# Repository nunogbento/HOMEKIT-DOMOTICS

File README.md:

# HOMEKIT-DOMOTICS

Personal collection of home-automation hardware and firmware around Apple HomeKit,
spanning multiple generations of boards and HomeKit integration techniques.

## Project layout

Each top-level folder is one project. Projects with a custom PCB have:

```
<Project>/
├── firmware/      one subfolder per firmware version (generation)
├── circuit/       PCB design files (.brd / .sch / .cam)
└── enclosure/     3D-printable bodies (where applicable)
```

Projects without a custom PCB omit `circuit/`, and use `enclosure/` only if a
3D-printed body exists.

## Active projects

### [PCCWDplus](PCCWDplus/) — custom PCB
Main panel board. Succession: MQTT (ESP8266) → HomeSpan (ESP32-C5).
Gen 2 (HAP/ESP8266) was attempted but failed; see archive notes.
- `firmware/Mqtt.MordomusESP8266/` — gen 1, MQTT/ESP8266 — **deployed**
- `firmware/HSPCCWDplus/` — gen 3, HomeSpan/ESP32-C5 — **WIP**, pin-compatible drop-in

### [MultiAccessory](MultiAccessory/) — custom PCB
Multi-device controller board. Gen 2 still deployed, gen 3 in progress.
- `firmware/HKMultiAccessory/` — gen 2, HAP/ESP8266 — **deployed**
- `firmware/HSPMultiAccessory/` — gen 3, HomeSpan/ESP32-C5 — **WIP**
- `firmware/HKSprinklerValve/` — gen 2 valve variant on the same board

### [ESP8266-ADC](ESP8266-ADC/) — custom PCB
Shared ESP8266-with-ADC board used for analog sensing applications.
- `firmware/HKSolarPanel/` — gen 2, HAP/ESP8266 — **deployed**, no successor planned
- `firmware/mqtt-SolarPanel/` — gen 1, archived firmware
- `firmware/Mqtt.ESP8266PlantComputer/` — gen 1, archived firmware

### [HSPCCWD](HSPCCWD/) — no custom hardware
HomeSpan reference implementation on a bare ESP32 devkit, serial-only.

### [ESP32Door](ESP32Door/) — no custom hardware
Door sensor using an off-the-shelf ESP32 module + 3D-printed enclosure.

### [Feeder](Feeder/) — no custom hardware, 3D-printed body
- `firmware/HKFEEDER/` — current
- `firmware/mqtt-RabitFeeder/` — earlier version

## HomeKit firmware generations

| Gen | Stack           | Chip         | Status                                |
|-----|-----------------|--------------|---------------------------------------|
| 1   | MQTT bridge     | ESP8266      | Mqtt.MordomusESP8266 still deployed   |
| 2   | Arduino-HomeKit | ESP8266      | HKMultiAccessory, HKSolarPanel still deployed; HKPCCWD archived (failed) |
| 3   | HomeSpan        | ESP32 / C5   | HSPCCWDplus, HSPMultiAccessory — WIP  |

Gen 2 failed on the PCCWD board because the ESP8266 could not handle HomeKit
at that board's accessory complexity. That's why the PCCWD lineage jumps
directly from gen 1 (MQTT) to gen 3 (HomeSpan).

## archive/

Everything superseded, retired, unfinished, unrelated, or not tied to an
active hardware project. Includes:
- `HKPCCWD/` (gen 2 failure)
- Early MQTT experiments (lightbulbs, rollerblinds, power meter, etc.)
- Side experiments (CameraWebServer, ESP-32CAM, SONOFFAPI, WaterDetector)
- `Tradfri-ICC-1/` — reverse-engineering research that informed MultiAccessory
- `MordomusAPI/`, `PowerMeter/`, `pccwdapi/`, `node-red-contrib-pccwd/` — no longer used
- `homebridge-host/` — Homebridge configuration, Node-RED flows, backups

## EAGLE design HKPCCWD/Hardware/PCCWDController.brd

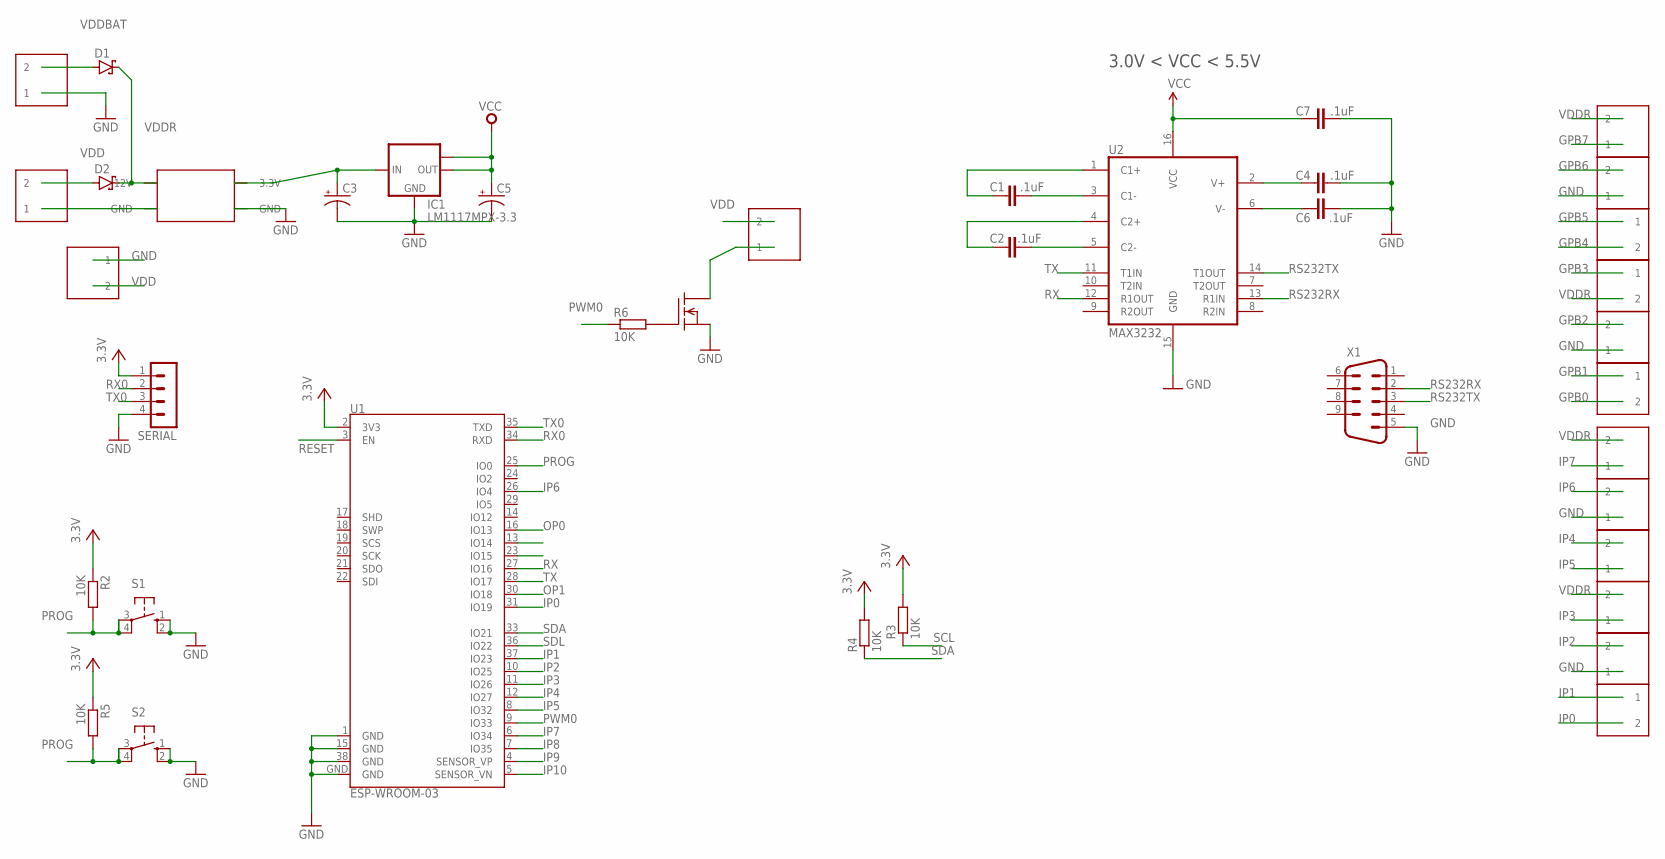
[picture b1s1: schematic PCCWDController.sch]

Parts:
C1, C2, C4, C6, C7: .1uF; 0603-CAP
C3, C5: 100UF-25V-20%(PTH); CPOL-RADIAL-100UF-25V
D1, D2: SCHOTTKY-DIODESMC; SMC
G: FDS5680; SO-8
IC1: LM1117MPX-3.3; SOT223
PWR1: MP2307-MINI-360
PWR_IN, PWR_IN1, PWR_IN2, PWR_IN3, PWR_IN4, PWR_IN5, PWR_IN6, PWR_IN7, PWR_IN8, PWR_IN9, PWR_IN10, PWR_IN11, PWR_IN12, PWR_IN13, PWR_IN14: KF350-P2; KF350-2P
PWR_INBAT: KF350-P2; KF350-2P
R2, R3, R4, R5, R6: 10K; R0603
S1, S2: 10-XX; B3F-10XX
SERIAL: MA04-1
U1: ESP-WROOM-03
U2: MAX3232; SO016
X1: M09HP

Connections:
+3V3: C5.1 (+), C7.1, IC1.2 (OUT), IC1.TAB (OUT1), R2.1, R3.2, R4.2, R5.1, SERIAL.1, U2.16 (VCC)
C1+: C1.1, U2.1 (C1+)
C1-: C1.2, U2.3 (C1-)
C2+: C2.1, U2.4 (C2+)
C2-: C2.2, U2.5 (C2-)
DG: G.5 (D), G.6 (D), G.7 (D), G.8 (D), PWR_IN1.1
GND: C3.2 (-), C4.2, C5.2 (-), C6.2, C7.2, G.1 (S), G.2 (S), G.3 (S), IC1.1 (GND), PWR1.GND@1 (GND), PWR1.GND@2 (GND), PWR_IN.1, PWR_IN2.1, PWR_IN5.1, PWR_IN8.1, PWR_IN12.1, PWR_IN14.1, PWR_INBAT.1, S1.1 (S), S1.2 (S1), S2.1 (S), S2.2 (S1), SERIAL.4, U1.1 (GND), U1.15 (GND), U1.38 (GND), U1.GND, U2.15 (GND), X1.5
GPB0: PWR_IN6.2
GPB1: PWR_IN6.1
GPB2: PWR_IN5.2
GPB3: PWR_IN7.1
GPB4: PWR_IN9.2
GPB5: PWR_IN9.1
GPB6: PWR_IN8.2
GPB7: PWR_IN4.1
IP0: PWR_IN11.2, U1.31 (IO19)
IP1: PWR_IN11.1, U1.37 (IO23)
IP2: PWR_IN12.2, U1.10 (IO25)
IP3: PWR_IN13.1, U1.11 (IO26)
IP4: PWR_IN3.2, U1.12 (IO27)
IP5: PWR_IN3.1, U1.8 (IO32)
IP6: PWR_IN2.2, U1.26 (IO4)
IP7: PWR_IN10.1, U1.6 (IO34)
IP8: U1.7 (IO35)
IP9: U1.4 (SENSOR_VP)
IP10: U1.5 (SENSOR_VN)
unnamed: G.4 (G), R6.2
OP0: U1.16 (IO13)
OP1: U1.30 (IO18)
PROG: R2.2, R5.2, S1.3, S1.4 (P1), S2.3, S2.4 (P1), U1.25 (IO0)
PWM0: R6.1, U1.9 (IO33)
RESET: U1.3 (EN)
RS232RX: U2.13 (R1IN), X1.2
RS232TX: U2.14 (T1OUT), X1.3
RVCC: C3.1 (+), IC1.3 (IN), PWR1.3.3V
RX: U1.27 (IO16), U2.12 (R1OUT)
RX0: SERIAL.2, U1.34 (RXD)
SCL: R3.1
SDA: R4.1, U1.33 (IO21)
SDL: U1.36 (IO22)
TX: U1.28 (IO17), U2.11 (T1IN)
TX0: SERIAL.3, U1.35 (TXD)
V+: C4.1, U2.2 (V+)
V-: C6.1, U2.6 (V-)
VCC: U1.2 (3V3)
VDD: D2.A, PWR_IN.2, PWR_IN1.2, PWR_IN14.2
VDDBAT: D1.A, PWR_INBAT.2
VDDR: D1.C, D2.C, PWR1.12V, PWR_IN4.2, PWR_IN7.2, PWR_IN10.2, PWR_IN13.2

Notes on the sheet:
3.0V < VCC < 5.5V

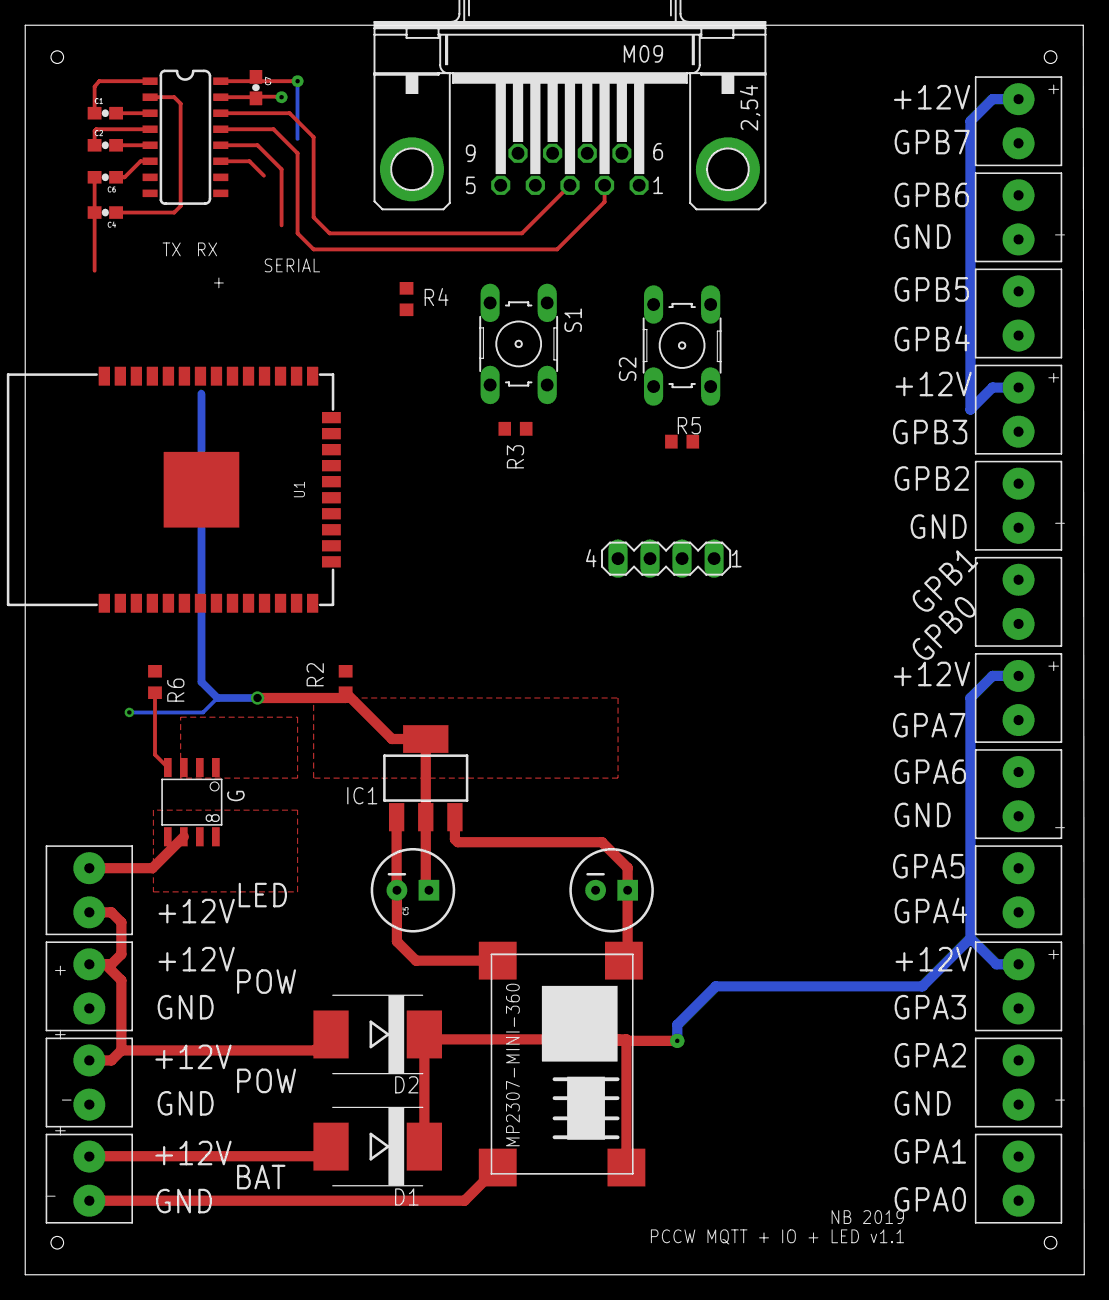
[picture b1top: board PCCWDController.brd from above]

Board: 2 copper layers, 83.9 x 99.0 mm, 39 parts (0 on the bottom side), 31 nets.

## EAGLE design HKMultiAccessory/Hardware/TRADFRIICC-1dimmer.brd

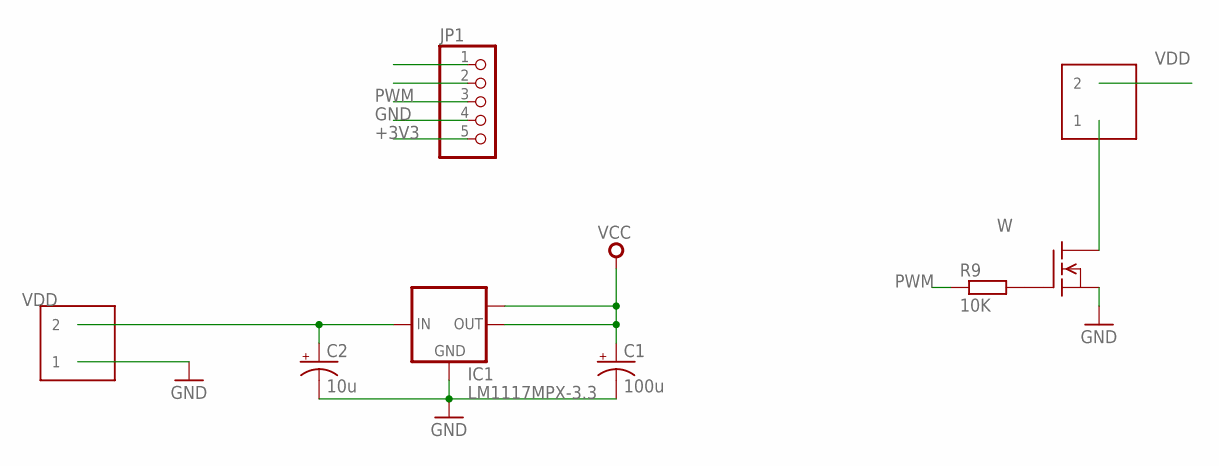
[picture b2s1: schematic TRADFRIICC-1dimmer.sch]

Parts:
C1: 100u; CT3528
C2: 10u; C/6032-28R
IC1: LM1117MPX-3.3; SOT223
JP1: PINHD-1X55X2MM; 1_05X2MM
PWR_IN, PWR_IN1: KF350-P2; KF350-2P
R9: 10K; R0603
W: FDS5680; SO-8

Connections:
+3V3: C1.+, IC1.2 (OUT), IC1.TAB (OUT1), JP1.5
DW: PWR_IN1.1, W.5 (D), W.6 (D), W.7 (D), W.8 (D)
GND: C1.-, C2.-, IC1.1 (GND), JP1.4, PWR_IN.1, W.1 (S), W.2 (S), W.3 (S)
unnamed: R9.2, W.4 (G)
PWM: JP1.3, R9.1
VDD: C2.+, IC1.3 (IN), PWR_IN.2, PWR_IN1.2

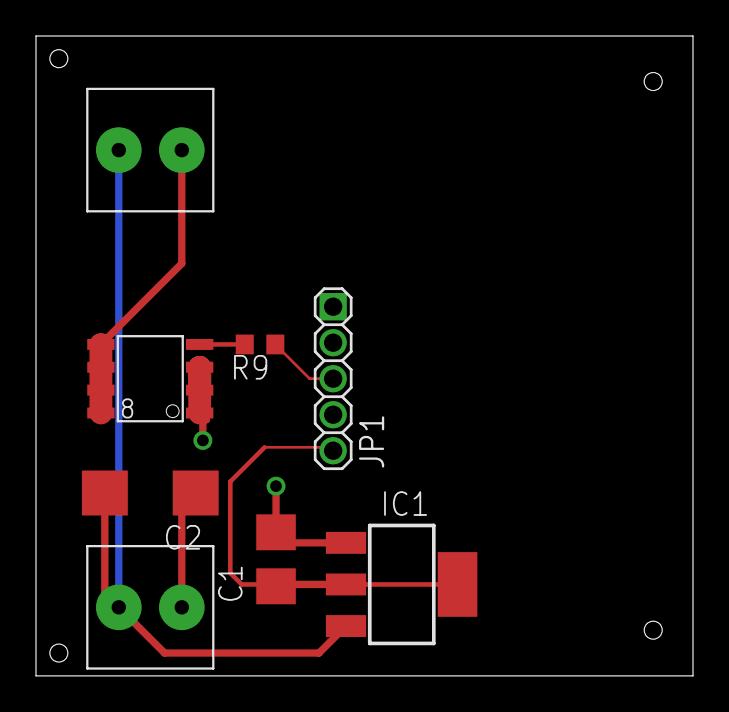
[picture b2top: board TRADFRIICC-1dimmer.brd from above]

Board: 2 copper layers, 36.5 x 35.5 mm, 8 parts (0 on the bottom side), 6 nets.

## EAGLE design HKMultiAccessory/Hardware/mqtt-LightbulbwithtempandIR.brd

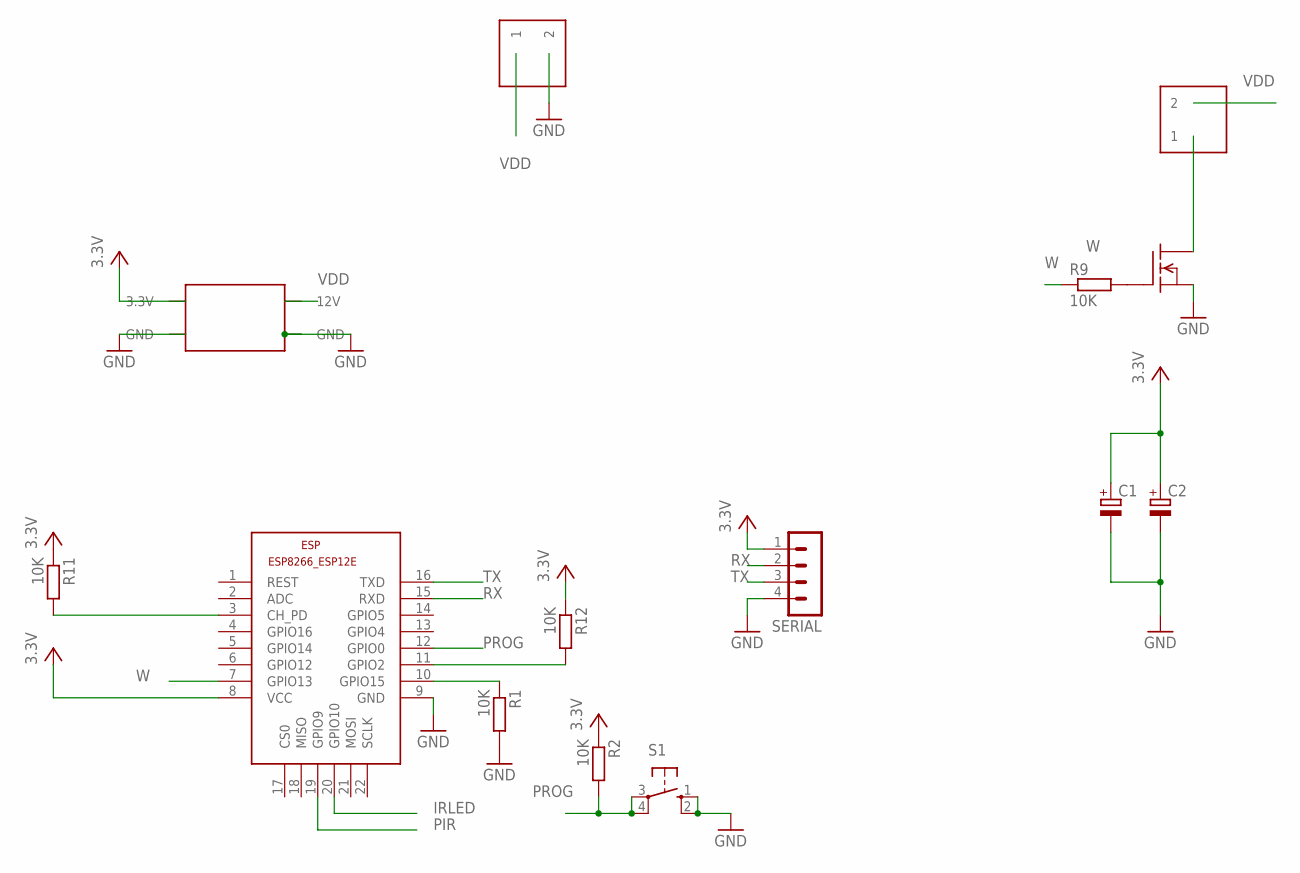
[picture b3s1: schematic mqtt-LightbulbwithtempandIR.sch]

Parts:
C1, C2: CPOL-EUE2-5; E2-5
ESP: ESP8266-12EESP8266-ESP12E; ESP8266-ESP12E
PWR1: MP2307-MINI-360
PWR_IN1, PWR_IN2: KF350-P2; KF350-2P
R1, R2, R9, R11, R12: 10K; R0603
S1: 10-XX; B3F-10XX
SERIAL: MA04-1
W: FDS5680; SO-8

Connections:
DW: PWR_IN1.1, W.5 (D), W.6 (D), W.7 (D), W.8 (D)
GND: C1.-, C2.-, ESP.9 (GND), PWR1.GND@1 (GND), PWR1.GND@2 (GND), PWR_IN2.2, R1.2, S1.1 (S), S1.2 (S1), SERIAL.4, W.1 (S), W.2 (S), W.3 (S)
IRLED: ESP.20 (GPIO10)
unnamed: ESP.10 (GPIO15), R1.1
unnamed: ESP.3 (CH_PD), R11.2
unnamed: ESP.11 (GPIO2), R12.2
unnamed: R9.2, W.4 (G)
PIR: ESP.19 (GPIO9)
PROG: ESP.12 (GPIO0), R2.2, S1.3, S1.4 (P1)
RX: ESP.15 (RXD), SERIAL.2
TX: ESP.16 (TXD), SERIAL.3
VCC: C1.+, C2.+, ESP.8 (VCC), PWR1.3.3V, R2.1, R11.1, R12.1, SERIAL.1
VDD: PWR1.12V, PWR_IN1.2, PWR_IN2.1
W: ESP.7 (GPIO13), R9.1

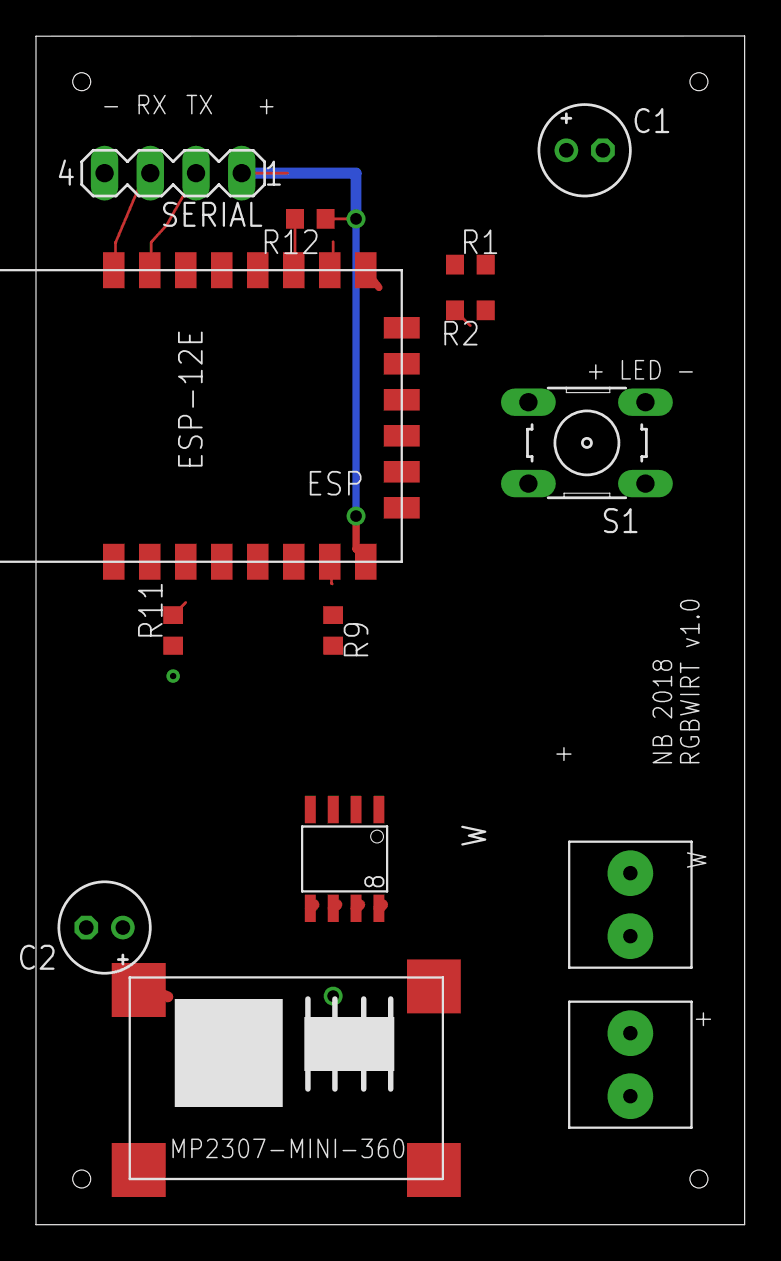
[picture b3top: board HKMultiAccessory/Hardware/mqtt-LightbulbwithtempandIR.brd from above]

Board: 2 copper layers, 39.4 x 66.0 mm, 14 parts (0 on the bottom side), 12 nets.

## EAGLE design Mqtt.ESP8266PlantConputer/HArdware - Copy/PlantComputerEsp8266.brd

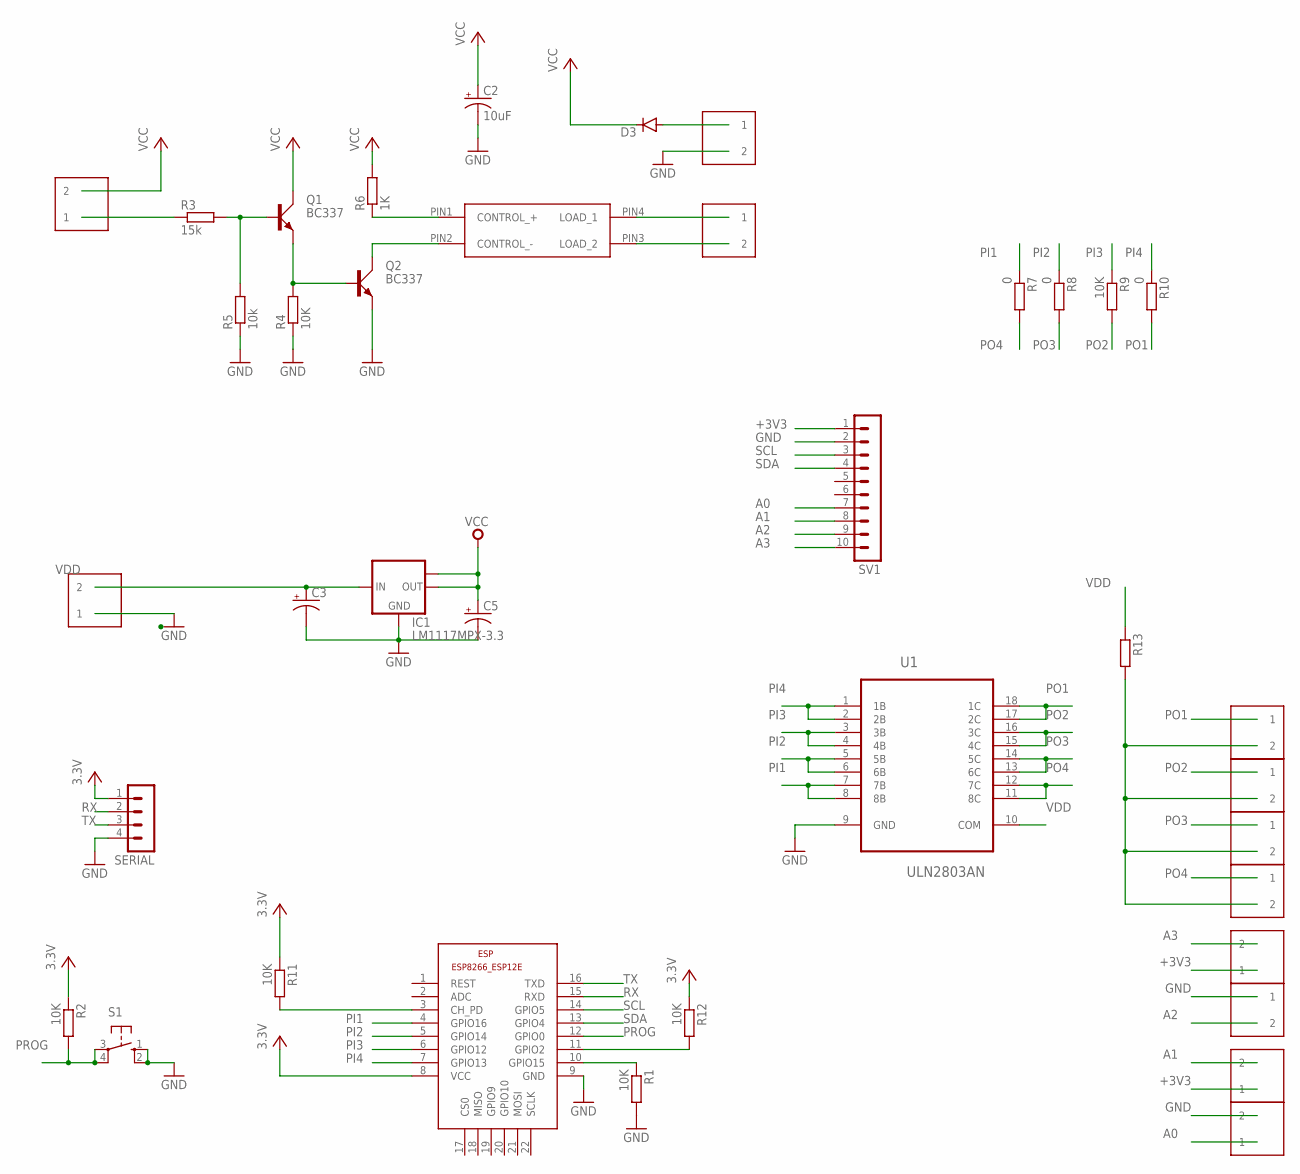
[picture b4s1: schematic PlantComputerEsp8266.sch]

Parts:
C2: 10uF; CPOL-RADIAL-2.5MM-5MM
C3, C5: 100UF-25V-20%(PTH); CPOL-RADIAL-100UF-25V
D3: DIODE-DO214AC; DO214AC
ESP: ESP8266-12EESP8266-ESP12E; ESP8266-ESP12E
IC1: LM1117MPX-3.3; SOT223
PWR_IN, PWR_IN2, PWR_IN4, PWR_IN5, PWR_IN6, PWR_IN7, PWR_IN8, PWR_IN9, PWR_IN10: KF350-P2; KF350-2P
Q1, Q2: BC337; SOT54A
R1, R2, R9, R11, R12: 10K; R0603
R3: 15k; R0805
R4: 10K; R0805
R5: 10k; R0805
R6: 1K; R0805
R7, R8, R10: 0; R0603
R13: R-EU_R0603; R0603
S1: 10-XX; B3F-10XX
SERIAL: MA04-1
SV1: MA10-1
U1: ULN2803AN; DIP254P762X393-18
U$1: OPTO-RELAY-CPC1017N; SOP-4
U$2, U$3, U$4: KF350-P2; KF350-2P

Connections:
+3V3: C5.1 (+), ESP.8 (VCC), IC1.2 (OUT), IC1.TAB (OUT1), PWR_IN5.1, PWR_IN10.1, R2.1, R11.1, R12.1, SERIAL.1, SV1.1
A0: PWR_IN2.1, SV1.7
A1: PWR_IN10.2, SV1.8
A2: PWR_IN6.2, SV1.9
A3: PWR_IN5.2, SV1.10
GND: C2.2 (-), C3.2 (-), C5.2 (-), ESP.9 (GND), IC1.1 (GND), PWR_IN.1, PWR_IN2.2, PWR_IN6.1, Q2.E, R1.2, R4.1, R5.1, S1.1 (S), S1.2 (S1), SERIAL.4, SV1.2, U1.9 (GND), U$3.2
unnamed: Q1.B, R3.2, R5.2
unnamed: ESP.10 (GPIO15), R1.1
unnamed: ESP.3 (CH_PD), R11.2
unnamed: ESP.11 (GPIO2), R12.2
unnamed: Q1.E, Q2.B, R4.2
unnamed: Q2.C, U$1.PIN2 (CONTROL_-)
unnamed: R6.1, U$1.PIN1 (CONTROL_+)
unnamed: R3.1, U$4.1
unnamed: U$1.PIN4 (LOAD_1), U$2.1
unnamed: D3.A, U$3.1
unnamed: U$1.PIN3 (LOAD_2), U$2.2
unnamed: PWR_IN4.2, PWR_IN7.2, PWR_IN8.2, PWR_IN9.2, R13.2
PI1: ESP.4 (GPIO16), R7.1, U1.7 (7B), U1.8 (8B)
PI2: ESP.5 (GPIO14), R8.1, U1.5 (5B), U1.6 (6B)
PI3: ESP.6 (GPIO12), R9.1, U1.3 (3B), U1.4 (4B)
PI4: ESP.7 (GPIO13), R10.1, U1.1 (1B), U1.2 (2B)
PO1: PWR_IN4.1, R10.2, U1.17 (2C), U1.18 (1C)
PO2: PWR_IN8.1, R9.2, U1.15 (4C), U1.16 (3C)
PO3: PWR_IN9.1, R8.2, U1.13 (6C), U1.14 (5C)
PO4: PWR_IN7.1, R7.2, U1.11 (8C), U1.12 (7C)
PROG: ESP.12 (GPIO0), R2.2, S1.3, S1.4 (P1)
RX: ESP.15 (RXD), SERIAL.2
SCL: ESP.14 (GPIO5), SV1.3
SDA: ESP.13 (GPIO4), SV1.4
TX: ESP.16 (TXD), SERIAL.3
VCC: C2.1 (+), D3.C, Q1.C, R6.2, U$4.2
VDD: C3.1 (+), IC1.3 (IN), PWR_IN.2, R13.1, U1.10 (COM)

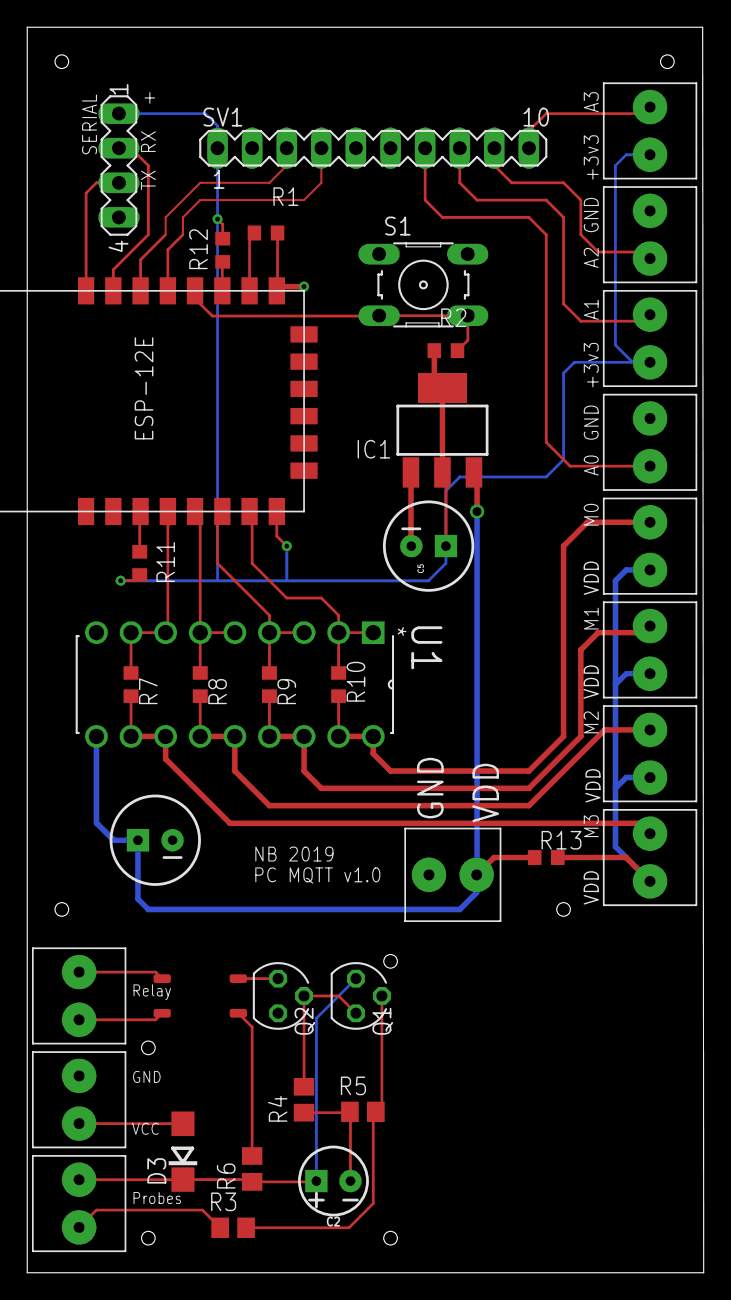
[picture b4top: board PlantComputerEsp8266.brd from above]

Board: 2 copper layers, 49.7 x 91.4 mm, 38 parts (0 on the bottom side), 33 nets.

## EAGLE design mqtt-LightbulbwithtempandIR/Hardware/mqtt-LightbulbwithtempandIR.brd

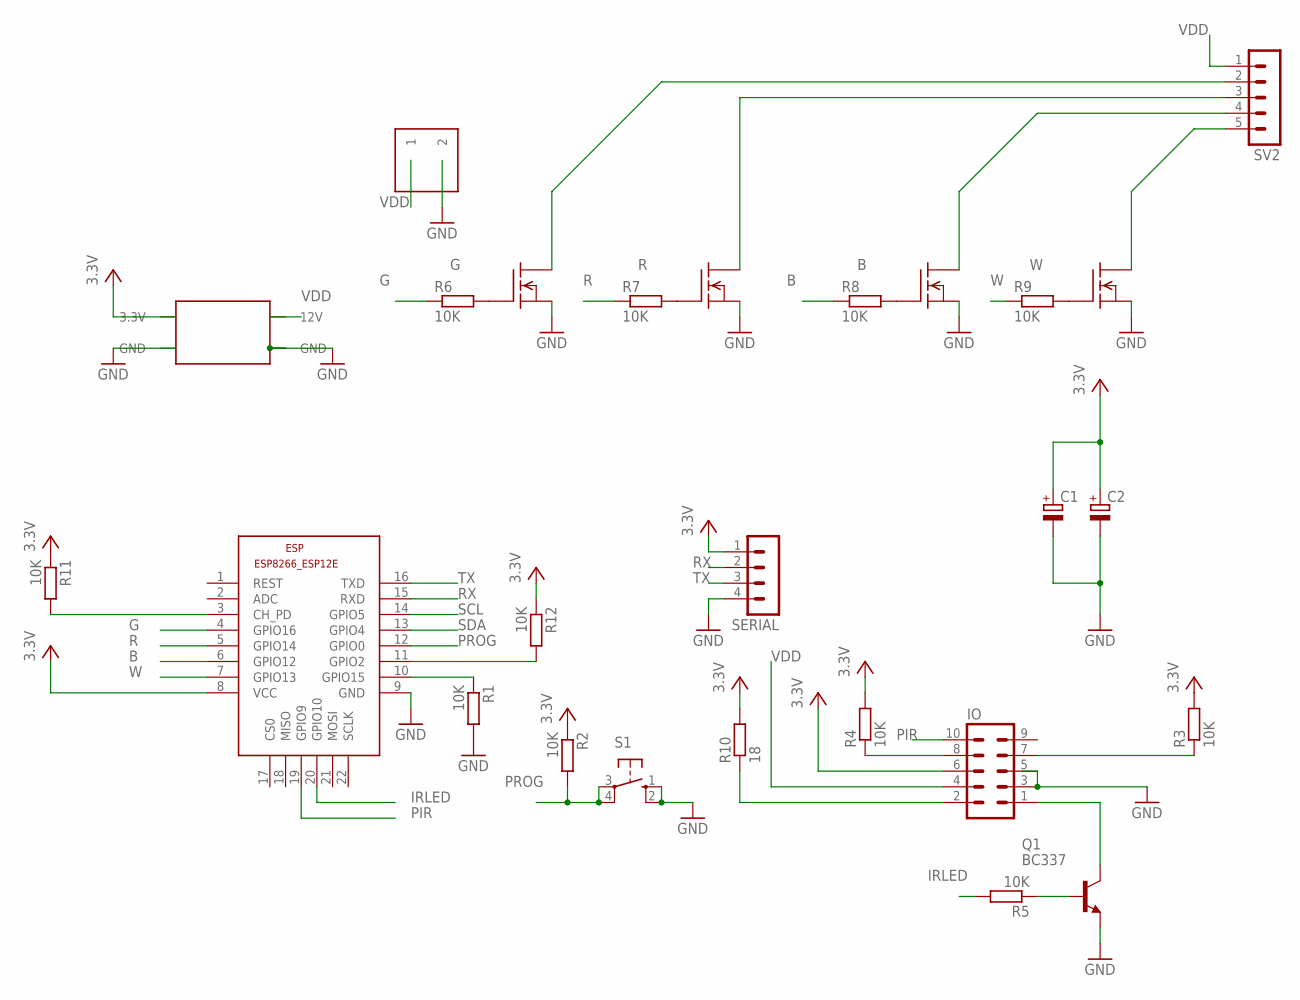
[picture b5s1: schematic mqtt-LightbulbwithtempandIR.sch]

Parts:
B: FDS5680; SO-8
C1, C2: CPOL-EUE2-5; E2-5
ESP: ESP8266-12EESP8266-ESP12E; ESP8266-ESP12E
G: FDS5680; SO-8
IO: MA05-2
PWR1: MP2307-MINI-360
PWR_IN: KF350-P2; KF350-2P
Q1: BC337; TO92
R: FDS5680; SO-8
R1, R2, R3, R4, R5, R6, R7, R8, R9, R11, R12: 10K; R0603
R10: 18; R0603
S1: 10-XX; B3F-10XX
SERIAL: MA04-1
SV2: MA05-1
W: FDS5680; SO-8

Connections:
B: ESP.6 (GPIO12), R8.1
DB: B.5 (D), B.6 (D), B.7 (D), B.8 (D), SV2.4
DG: G.5 (D), G.6 (D), G.7 (D), G.8 (D), SV2.2
DR: R.5 (D), R.6 (D), R.7 (D), R.8 (D), SV2.3
DW: SV2.5, W.5 (D), W.6 (D), W.7 (D), W.8 (D)
G: ESP.4 (GPIO16), R6.1
GND: B.1 (S), B.2 (S), B.3 (S), C1.-, C2.-, ESP.9 (GND), G.1 (S), G.2 (S), G.3 (S), IO.3, IO.5, PWR1.GND@1 (GND), PWR1.GND@2 (GND), PWR_IN.2, Q1.1 (E), R.1 (S), R.2 (S), R.3 (S), R1.2, S1.1 (S), S1.2 (S1), SERIAL.4, W.1 (S), W.2 (S), W.3 (S)
IRLED: ESP.20 (GPIO10), R5.2
unnamed: ESP.10 (GPIO15), R1.1
unnamed: ESP.3 (CH_PD), R11.2
unnamed: ESP.11 (GPIO2), R12.2
unnamed: G.4 (G), R6.2
unnamed: Q1.2 (B), R5.1
unnamed: R.4 (G), R7.2
unnamed: B.4 (G), R8.2
unnamed: R9.2, W.4 (G)
unnamed: IO.2, R10.1
unnamed: IO.1, Q1.3 (C)
PIR: ESP.19 (GPIO9), IO.10
PROG: ESP.12 (GPIO0), R2.2, S1.3, S1.4 (P1)
R: ESP.5 (GPIO14), R7.1
RX: ESP.15 (RXD), SERIAL.2
SCL: ESP.14 (GPIO5), IO.7, R3.1
SDA: ESP.13 (GPIO4), IO.8, R4.1
TX: ESP.16 (TXD), SERIAL.3
VCC: C1.+, C2.+, ESP.8 (VCC), IO.6, PWR1.3.3V, R2.1, R3.2, R4.2, R10.2, R11.1, R12.1, SERIAL.1
VDD: IO.4, PWR1.12V, PWR_IN.1, SV2.1
W: ESP.7 (GPIO13), R9.1

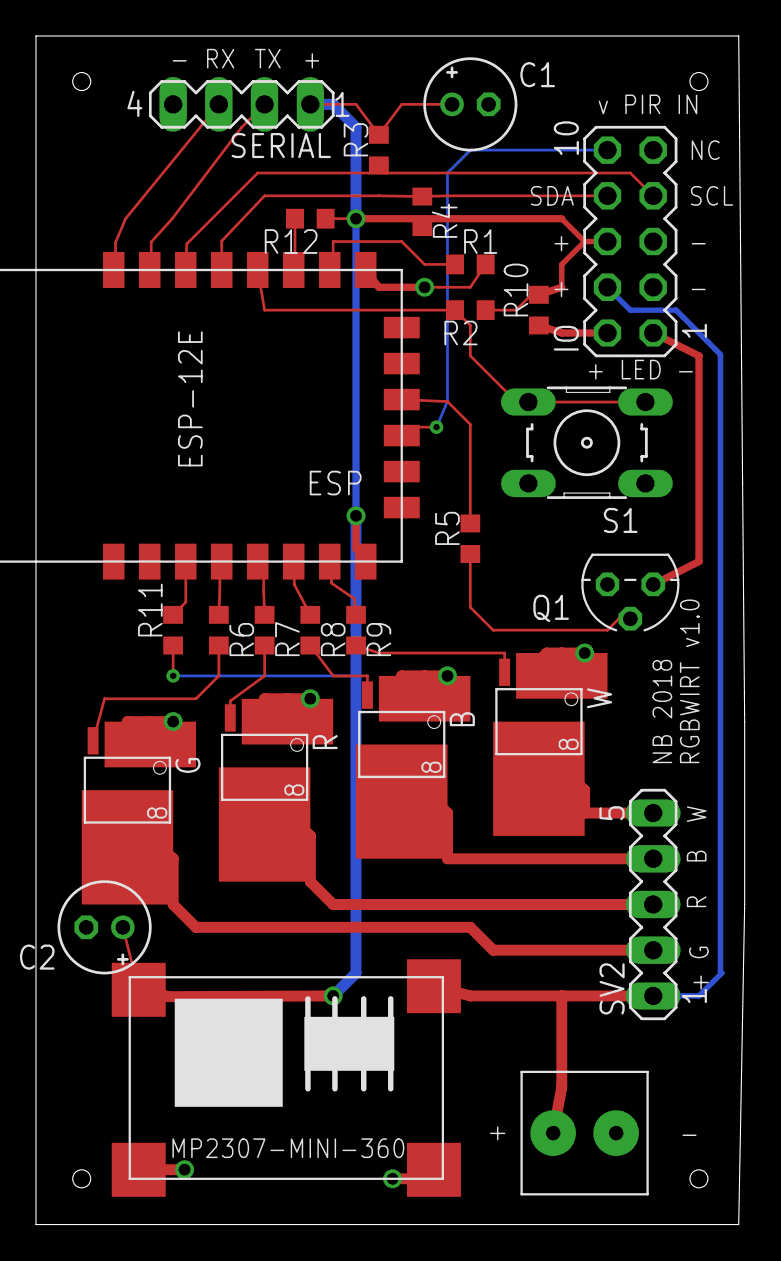
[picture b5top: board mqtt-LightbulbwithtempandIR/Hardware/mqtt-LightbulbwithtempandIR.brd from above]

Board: 2 copper layers, 39.4 x 66.0 mm, 26 parts (0 on the bottom side), 28 nets.

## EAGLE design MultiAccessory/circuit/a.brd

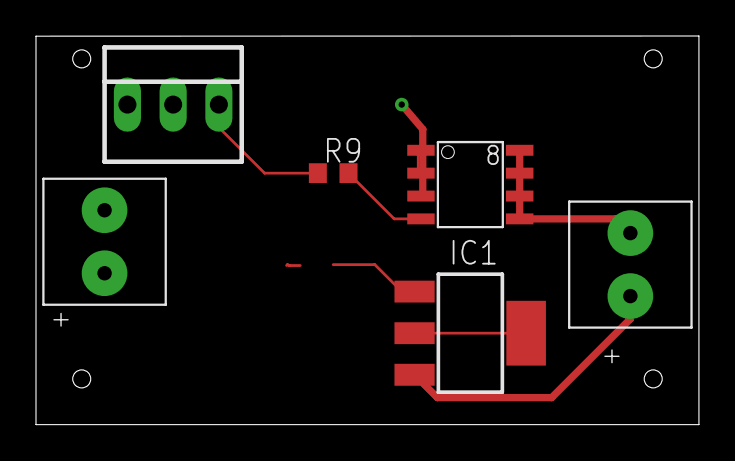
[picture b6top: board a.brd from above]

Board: 2 copper layers, 36.8 x 21.6 mm, 6 parts (0 on the bottom side), 6 nets.

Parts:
IC1: LM1117MPX-3.3; SOT223
PWR_IN, PWR_IN1: KF350-P2; KF350-2P
R9: 10K; R0603
W: SO-8
X1: 22-23-2031

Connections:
+3V3: IC1.2, IC1.TAB
DW: PWR_IN1.1, W.5, W.6, W.7, W.8
GND: IC1.1, PWR_IN.1, W.1, W.2, W.3, X1.2
unnamed: R9.2, W.4
PWM: R9.1, X1.3
VDD: IC1.3, PWR_IN1.2

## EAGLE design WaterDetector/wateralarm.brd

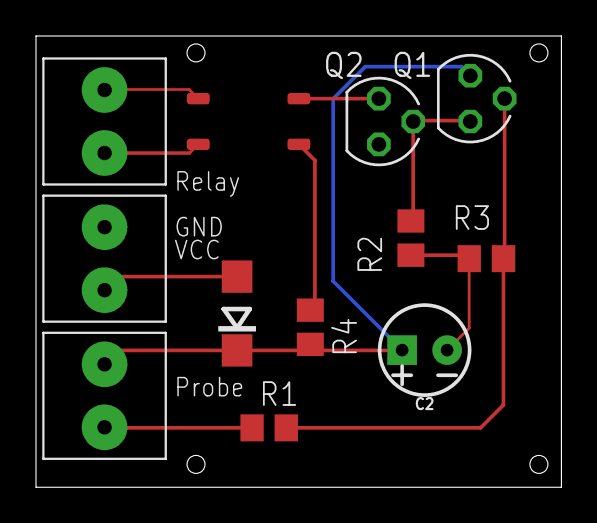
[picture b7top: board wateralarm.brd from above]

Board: 2 copper layers, 29.2 x 25.1 mm, 12 parts (0 on the bottom side), 10 nets.

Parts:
C2: 10uF; CPOL-RADIAL-2.5MM-5MM
D3: DO214AC
Q1, Q2: BC337; SOT54A
R1: R0805
R2: 10K; R0805
R3: 10k; R0805
R4: 1K; R0805
U$1: OPTO-RELAY-CPC1017N; SOP-4
U$2, U$3, U$4: KF350-P2; KF350-2P

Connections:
GND: C2.2, Q2.E, R2.1, R3.1, U$3.2
unnamed: Q1.B, R1.2, R3.2
unnamed: Q1.E, Q2.B, R2.2
unnamed: Q2.C, U$1.PIN2
unnamed: R4.1, U$1.PIN1
unnamed: R1.1, U$4.1
unnamed: U$1.PIN4, U$2.1
unnamed: U$1.PIN3, U$2.2
unnamed: D3.A, U$3.1
VCC: C2.1, D3.C, Q1.C, R4.2, U$4.2

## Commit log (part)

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2017-01-22 working
2017-01-22 fixes
2018-01-08 no message
2018-01-09 Wifi Manager
2018-01-09 cleanup
2018-01-13 temp & humidity sensor added, hardware ok
2018-01-14 motion sensor
2018-04-23 rabbit feeder
2018-04-30 PCCWD API with Initialization, power loss resilience. Mordomus Lights moved to mqtt plugin
2018-05-02 PCCWD mqtt set + nodered flows update
2018-06-04 fix config + IR implented
2018-07-02 added
2019-06-25 woking pccwd io
2019-08-12 working pccwd API
2019-08-12 settings prj
2019-11-05 stuff
2019-11-05 Copy for PCB Order
2020-04-08 Working Plan Computer + Box
2020-05-15 fixed crash
2020-05-16 less verbose log
2021-03-18 valvetype
2021-05-14 testing begins
2021-05-14 basic on/of OK dimmer OK fixes
2021-05-14 LED dual and dual dimmer OK
2021-05-14 LEDController ok only hsi2RGB not that good
2021-05-14 temperature sensor ok
2021-05-14 AC compiling
2021-05-14 ac pregress but not good yet
2021-05-15 OTA Good, AC not crashing but still acting up.
2021-05-17 deployed
2021-05-17 AC ALL Good now
2021-05-18 hksolarpanel added
2021-05-18 hksp compiling
2021-05-18 changed ac
2021-05-21 fixes on AC controller
2021-05-29 hkpccwd
2021-06-04 New Hmespan Based ESP32 PCCWD controller working
2022-01-20 added temp log via mqtt + fixes
2023-03-21 Sofware hanges
2023-03-21 Board updates
2024-05-15 HK irrigation valves
2024-05-15 Bridge Version
2024-05-16 back to single accessory. valve 4 fixed.
2024-05-17 hksprinkler loop and calbacks done
2024-09-06 PCCWD updated dependencies
2024-09-06 Improved Homebridge sync
2024-09-06 Update PCCWDAPo.ino
    Added NO Motion Sensor support
2024-09-10 bug fixing
2024-10-13 minor stuff
2025-06-16 Created hsp muliaccessory for esp32c6
2025-06-16 merge
2025-06-17 Implementation of hspmultiaccessory
2025-06-17 ac reviwwd
2025-06-20 working almost
2025-06-21 AC making sense now
2025-06-22 tunning
2025-06-23 alternative mode AC test
2025-06-23 refining hspmultiaccessory
2025-06-24 DONE HSP multiaccessory
2025-06-24 hspmultiaccessory final
2026-04-17 move
2026-06-18 Doorbel phase 1
2026-06-18 moving

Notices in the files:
parts and their libraries:
SparkFun-Capacitors: Licensing: Creative Commons ShareAlike 4.0 International - https://creativecommons.org/licenses/by-sa/4.0
SparkFun-DigitalIC: Licensing: CC v3.0 Share-Alike You are welcome to use this library for commercial purposes.
